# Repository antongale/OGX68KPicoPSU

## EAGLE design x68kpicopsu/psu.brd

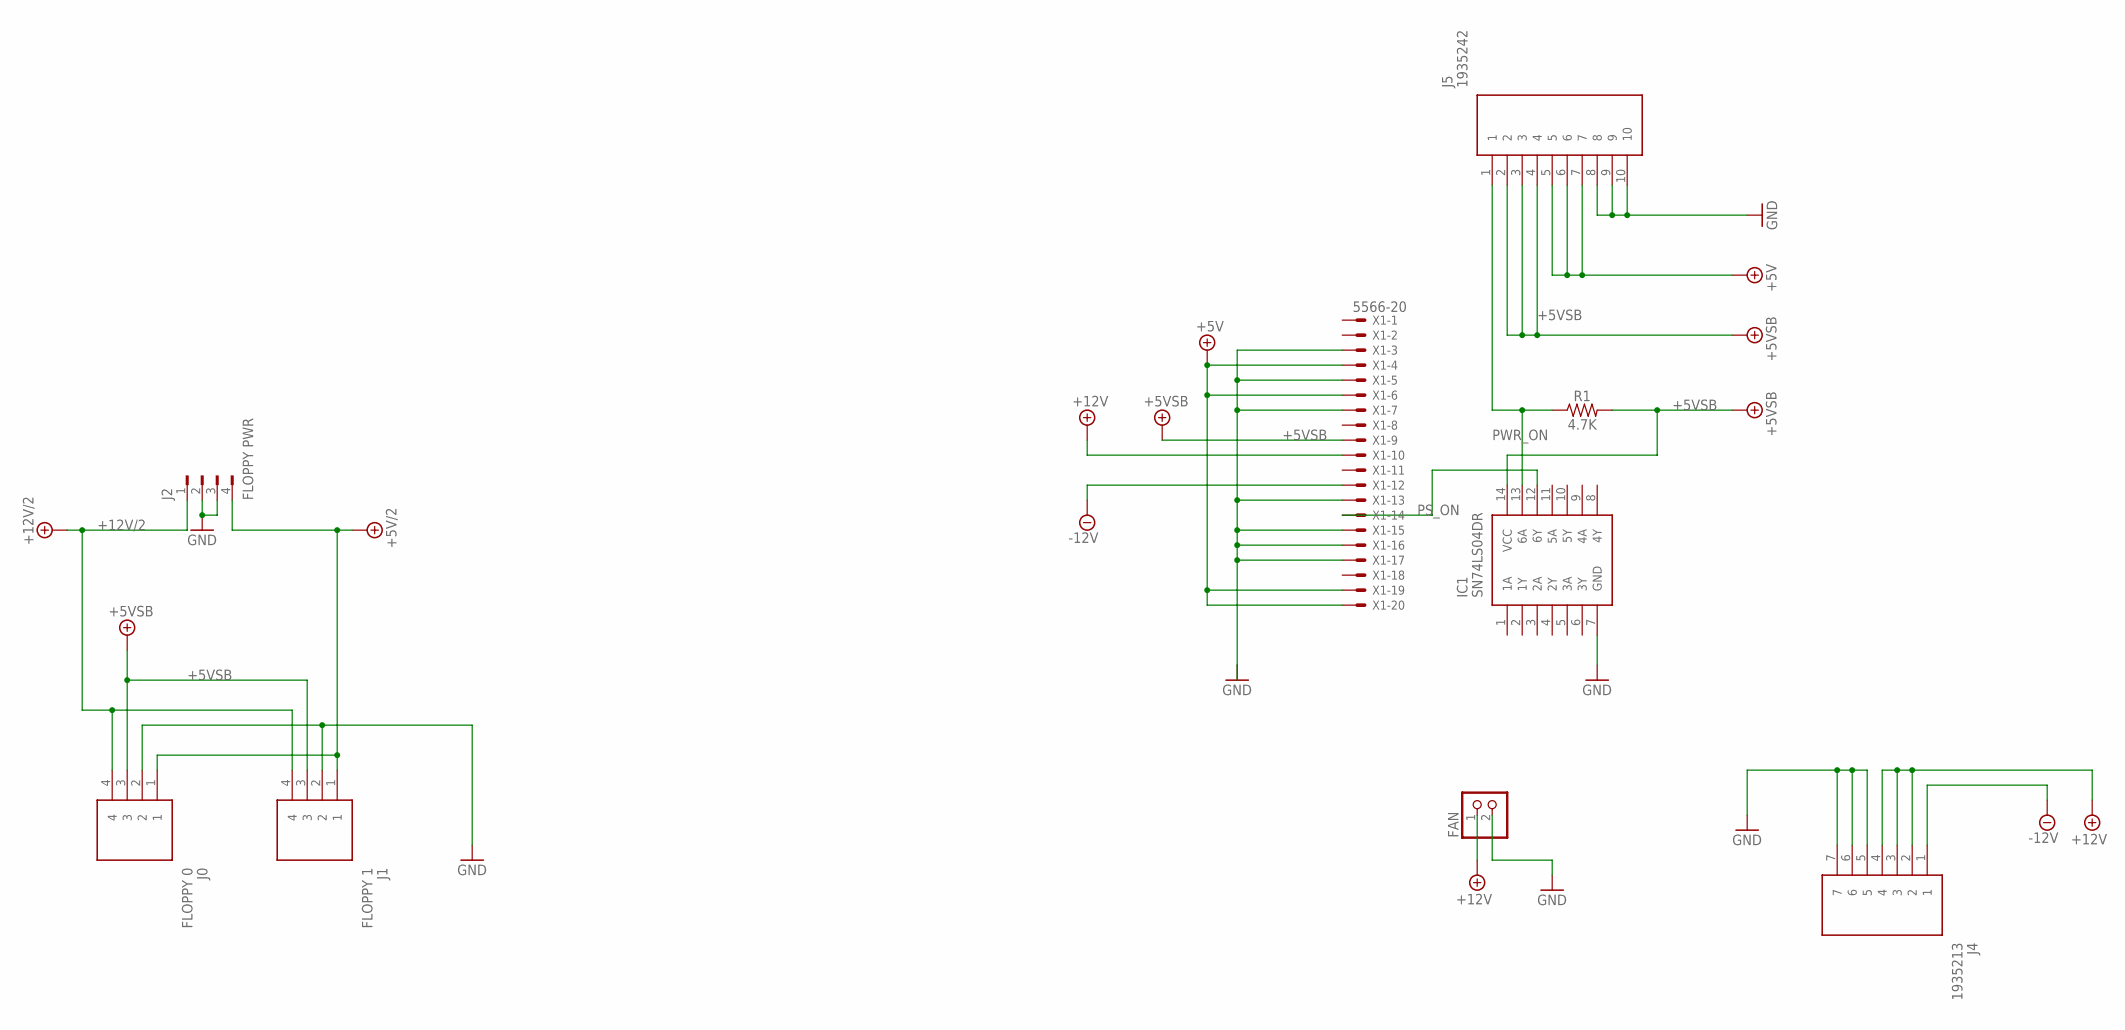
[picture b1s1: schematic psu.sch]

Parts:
FAN: PINHD-1X2; 1X02
IC1: SN74LS04DR; SOIC127P600X175-14N
J0: FLOPPY 0; HDRV4W69P0X250_1X4_1000X500X10
J1: FLOPPY 1; HDRV4W69P0X250_1X4_1000X500X10
J2: FLOPPY PWR; 350211
J4: 1935213
J5: 1935242; SHDR10W130P0X500_1X10_5000X850
R1: 4.7K; 0805
X1: 5566-20

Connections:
+5V: J5.5, J5.6, J5.7, X1.4, X1.6, X1.19, X1.20
+5V/2: J0.1, J1.1, J2.4
+5VSB: IC1.14 (VCC), J0.3, J1.3, J5.2, J5.3, J5.4, R1.2, X1.9
+12V: FAN.1, J4.2, J4.3, J4.4, X1.10
+12V/2: J0.4, J1.4, J2.1
-12V: J4.1, X1.12
GND: FAN.2, IC1.7 (GND), J0.2, J1.2, J2.2, J2.3, J4.5, J4.6, J4.7, J5.8, J5.9, J5.10, X1.3, X1.5, X1.7, X1.13, X1.15, X1.16, X1.17
PS_ON: IC1.12 (6Y), X1.14
PWR_ON: IC1.13 (6A), J5.1, R1.1

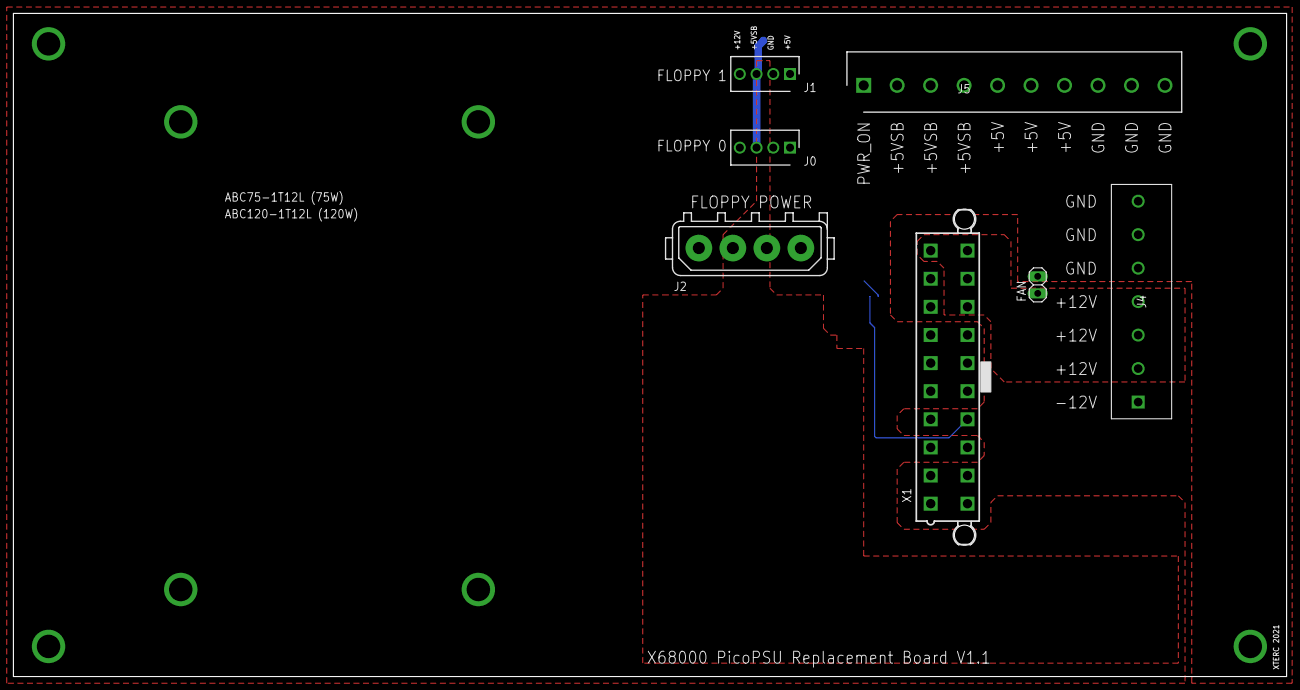
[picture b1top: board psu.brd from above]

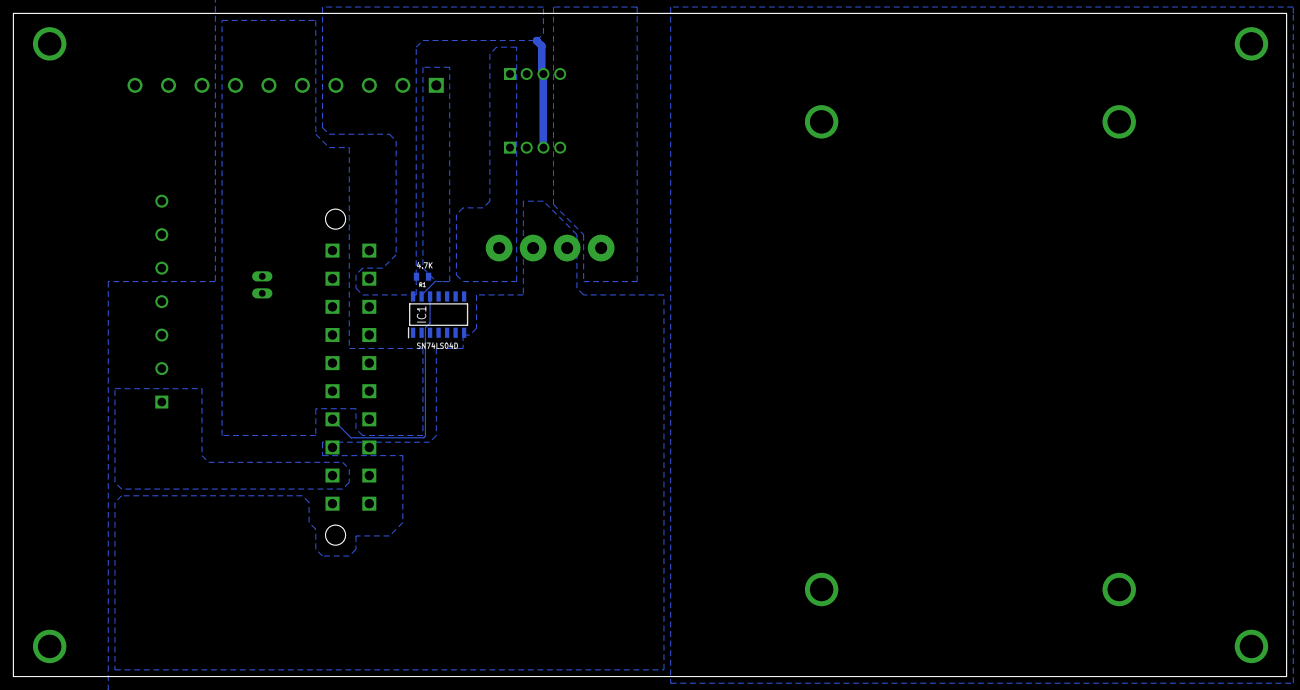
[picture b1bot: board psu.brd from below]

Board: 2 copper layers, 190.2 x 99.0 mm, 9 parts (2 on the bottom side), 9 nets.

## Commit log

2021-12-25 Initial Eagle Files Commit
2021-12-25 Manufacturing files
2021-12-25 Bill of Materials

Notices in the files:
parts and their libraries:
SparkFun-Resistors: Licensing: Creative Commons ShareAlike 4.0 International - https://creativecommons.org/licenses/by-sa/4.0
